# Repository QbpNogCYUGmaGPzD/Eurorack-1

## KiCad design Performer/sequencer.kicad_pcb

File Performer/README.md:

# Performer Eurorack Sequencer
Modified for PJ398/366 Jacks

[Revised BOM][BOM]. <- Please Read, important changes

[Orginal Hardware][westlicht]

This work is licensed under a [Creative Commons Attribution-NonCommercial-ShareAlike 4.0 International License][CCBYNCSA].

[westlicht]: https://github.com/westlicht/performer-hardware
[BOM]: https://docs.google.com/spreadsheets/d/1Ij7JMWFCJfHYTZfkfIStLHR7a7g3nUJE4kBo3WPE5Zw/edit?usp=sharing
[CCBYNCSA]: http://creativecommons.org/licenses/by-nc-sa/4.0/

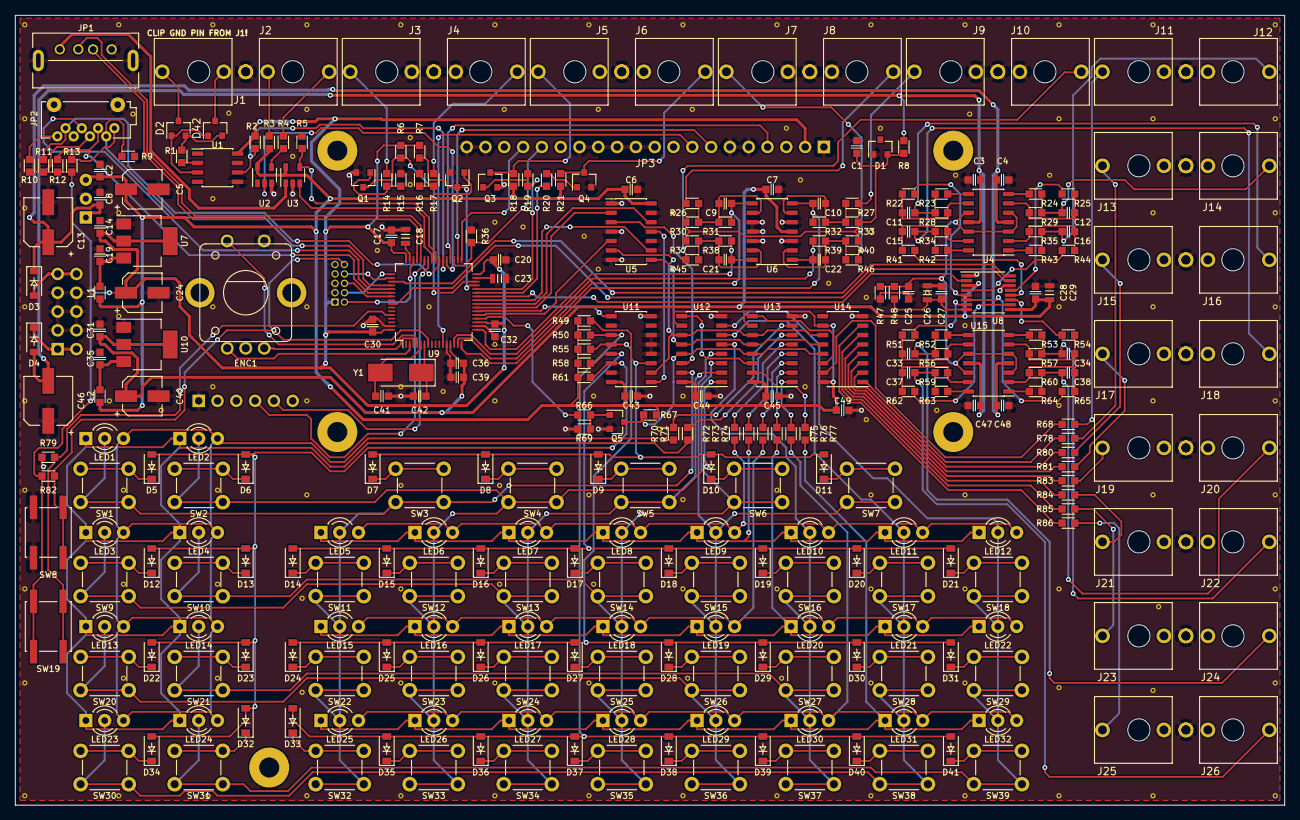
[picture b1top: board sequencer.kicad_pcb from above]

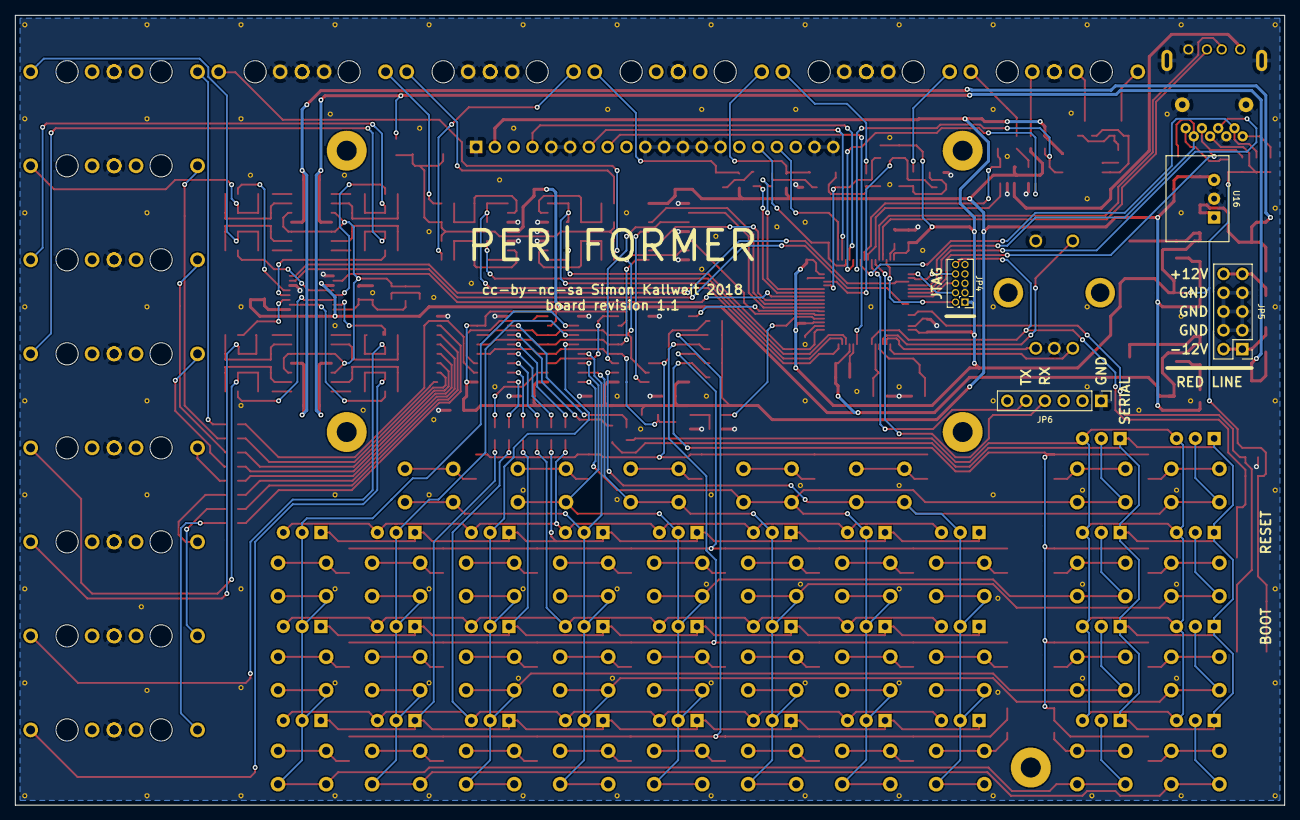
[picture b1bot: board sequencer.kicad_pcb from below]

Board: 2 copper layers, 171.4 x 106.7 mm, 305 parts (4 on the bottom side), 209 nets.

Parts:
C1, C2, C3, C4, C6, C7, C8, C14, C17, C19, C20, C25, C27, C28, C30, C31, C32, C35, C36, C43, C44, C45, C47, C48, C49: 100n; C_0603
C5, C24, C40: 22u; CP_Elec_5x5.8
C9, C10, C21, C22: 1n; C_0603
C11, C12, C15, C16, C33, C34, C37, C38, C41, C42: 18p; C_0603
C13, C46: 47u; CP_Elec_6.3x5.7
C18, C23, C26, C29: 2.2u; C_0805
C39: 1u; C_0603
D1: LM4040CIM3-10.0; SOT-23
D2, D42: BAT54S; SOT-23
D3, D4: 1N5819HW; D_SOD-123
D5, D6, D7, D8, D9, D10, D11, D12, D13, D14, D15, D16, D17, D18, D19, D20, D21, D22, D23, D24, D25, D26, D27, D28, D29, D30, D31, D32, D33, D34, D35, D36, D37, D38, D39, D40, D41: 1N4148; D_SOD-123
ENC1: PEC11R; ALPS_STEC12E08
J1, J2: PJ301CM; thonkiconn_tip3
J3, J4, J5, J6, J7, J8, J9, J10, J11, J12, J13, J14, J15, J16, J17, J18, J19, J20, J21, J22, J23, J24, J25, J26: PJ301BM; thonkiconn_tip3
JP1: USB_A; Kycon_USB_KUSBVLPX-AS1N
JP2: PJS008U-3000; PJS008U-3000-0
JP3: NHD-3.12-25664UC
JP4: JTAG; Pin_Header_Straight_2x05_Pitch1.27mm
JP5: POWER; Pin_Header_Straight_2x05_Pitch2.54mm
JP6: Serial / Bootloader; Pin_Header_Straight_1x06_Pitch2.54mm
L1, L2: Bead; R_0603
LED1, LED2, LED3, LED4, LED5, LED6, LED7, LED8, LED9, LED10, LED11, LED12, LED13, LED14, LED15, LED16, LED17, LED18, LED19, LED20, LED21, LED22, LED23, LED24, LED25, LED26, LED27, LED28, LED29, LED30, LED31, LED32: LTL1BEKVJNN
Q1, Q2, Q3, Q4, Q5: MMBT3904; SOT-23
R1, R3, R4, R23, R24, R42, R43, R52, R53, R63, R64: 220; R_0603
R2, R5, R6, R7, R19, R20, R36, R49, R50, R55, R58, R61, R66, R67, R79, R82: 10k; R_0603
R8, R18, R21, R68, R70, R71, R72, R73, R74, R75, R76, R77, R78, R80, R81, R83, R84, R85, R86: 1k; R_0603
R9, R15, R16: 1M; R_0603
R10, R11, R12, R13, R31, R32, R38, R39, R48: 33k; R_0603
R14, R17, R26, R27, R28, R29, R34, R35, R45, R46, R56, R57, R59, R60, R69: 100k; R_0603
R22, R25, R41, R44, R51, R54, R62, R65: 24k; R_0603
R30, R33, R37, R40: 200k; R_0603
R47: 22k; R_0603
SW1, SW2, SW3, SW4, SW5, SW6, SW7, SW9, SW10, SW11, SW12, SW13, SW14, SW15, SW16, SW17, SW18, SW20, SW21, SW22, SW23, SW24, SW25, SW26, SW27, SW28, SW29, SW30, SW31, SW32, SW33, SW34, SW35, SW36, SW37, SW38, SW39: TL1105; TL1105T
SW8, SW19: EVQQ2; SW_SPST_EVQQ2
U1: VO0600T; SOIC-8_3.9x4.9mm_Pitch1.27mm
U2: 74LV1T34; SOT-23-5
U3: STMPS2151; SOT-23-5
U4, U15: OPA4172; SOIC-14_3.9x8.7mm_Pitch1.27mm
U5: 74HCT125; SOIC-14_3.9x8.7mm_Pitch1.27mm
U6: MCP6004; SOIC-14_3.9x8.7mm_Pitch1.27mm
U7, U10: LM1117-3.3; SOT-223-3Lead_TabPin2
U8: DAC8568C; TSSOP-16_4.4x5mm_Pitch0.65mm
U9: STM32F405RGTx; LQFP-64_10x10mm_Pitch0.5mm
U11: 74HC165; SOIC-16_3.9x9.9mm_Pitch1.27mm
U12, U13, U14: 74HC595; SOIC-16_3.9x9.9mm_Pitch1.27mm
U16: R-78E5.0-1.0; R-78E-1.0
Y1: 8MHz; Crystal_SMD_Abracon_ABM3-2pin_5.0x3.2mm_HandSoldering

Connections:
+3.3VA: C7.1, C28.1, C29.1, C31.1, C36.1, C39.1, C40.1, U6.4, U8.3, U8.9, U9.13, U10.2
+3V3: C14.1, C17.1, C20.1, C24.1, C30.1, C32.1, JP2.4, JP3.2, JP4.1, R2.1, R6.1, R7.1, R10.2, R11.2, R12.2, R13.2, R82.1, SW19.2, U1.8, U7.2, U9.19, U9.32, U9.48, U9.64
+5V: C2.1, C5.1, C6.1, C43.1, C44.1, C45.1, C49.1, L1.2, L2.2, R3.1, R18.1, R21.1, R49.1, R50.1, R55.1, R58.1, R61.1, R67.1, U2.5, U3.5, U5.14, U11.16, U12.10, U12.16, U13.10, U13.16, U14.10, U14.16, U16.3
+12V: C4.1, C8.1, C13.1, C48.1, D3.1, U4.4, U15.4, U16.1
-12V: C3.2, C46.2, C47.2, D4.2, R8.1, U4.11, U15.11
/DAC/VBIAS: C25.1, R47.1, R48.2, U4.3, U4.5, U4.10, U4.12, U15.3, U15.5, U15.10, U15.12
AREF_-10V: C1.1, D1.2, R8.2, R30.2, R33.2, R37.2, R40.2
BOOT: R79.1, SW19.1, U9.60
CLK_IN: Q1.3, R6.2, U9.30
CLK_OUT: R19.2, U9.28
CV1: C16.1, J12.3, R35.1, R43.1
CV1_IN: C22.1, R39.1, U6.1, U9.14
CV2: C12.1, J14.3, R24.1, R29.1
CV2_IN: C9.1, R31.1, U6.8, U9.15
CV3: C11.1, J16.3, R23.1, R28.1
CV3_IN: C10.1, R32.1, U6.7, U9.16
CV4: C15.1, J18.3, R34.1, R42.1
CV4_IN: C21.1, R38.1, U6.14, U9.17
CV5: C38.1, J20.3, R60.1, R64.1
CV6: C34.1, J22.3, R53.1, R57.1
CV7: C33.1, J24.3, R52.1, R56.1
CV8: C37.1, J26.3, R59.1, R63.1
DAC1: R44.2, U8.4
DAC2: R25.2, U8.13
DAC3: R22.2, U8.5
DAC4: R41.2, U8.12
DAC5: R65.2, U8.6
DAC6: R54.2, U8.11
DAC7: R51.2, U8.7
DAC8: R62.2, U8.10
DAC_MOSI: U8.15, U9.57
DAC_SCK: U8.16, U9.51
DAC_SYNC: U8.2, U9.26
ENC_A: ENC1.A, U9.2
ENC_B: ENC1.B, U9.3
ENC_SW: ENC1.SW1, U9.4
GATE1: R68.2, U14.15
GATE2: R78.2, U14.1
GATE3: R80.2, U14.2
GATE4: R81.2, U14.3
GATE5: R83.2, U14.4
GATE6: R84.2, U14.5
GATE7: R85.2, U14.6
GATE8: R86.2, U14.7
GCOL0: LED25.3, LED26.3, LED27.3, LED28.3, LED29.3, LED30.3, LED31.3, LED32.3, R76.1
GCOL1: LED15.3, LED16.3, LED17.3, LED18.3, LED19.3, LED20.3, LED21.3, LED22.3, R74.1
GCOL2: LED5.3, LED6.3, LED7.3, LED8.3, LED9.3, LED10.3, LED11.3, LED12.3, R72.1
GCOL3: LED1.3, LED2.3, LED3.3, LED4.3, LED13.3, LED14.3, LED23.3, LED24.3, R70.1
GND: C1.2, C2.2, C3.1, C4.2, C5.2, C6.2, C7.2, C8.2, C13.2, C14.2, C17.2, C18.1, C19.2, C20.2, C23.1, C24.2, C25.2, C26.2, C27.2, C28.2, C29.2, C30.2, C31.2, C32.2, C35.2, C36.2, C39.2, C40.2, C41.1, C42.1, C43.2, C44.2, C45.2, C46.1, C47.1, C48.2, C49.2, D1.1, ENC1.C, ENC1.SW2, J1.1, J2.1, J3.1, J3.2, J4.1, J4.2, J5.1, J6.1, J7.1, J7.2, J8.1, J8.2, J9.1, J9.2, J10.1, J10.2, J11.1, J12.1, J13.1, J14.1, J15.1, J16.1, J17.1, J18.1, J19.1, J20.1, J21.1, J22.1, J23.1, J24.1, J25.1, J26.1, JP1.4, JP1.5, JP2.6, JP2.9, JP3.1, JP3.5, JP3.6, JP3.10, JP3.11, JP3.12, JP3.13, JP3.14, JP3.19, JP3.20, JP4.3, JP4.5, JP4.9, JP5.3, JP5.4, JP5.5, JP5.6, JP5.7, JP5.8, JP6.1, Q1.2, Q2.2, Q3.2, Q4.2, Q5.2, R5.2, R9.1, R15.2, R16.2, R36.2, R47.2, R69.2, R79.2, SW8.1, U1.5, U2.3, U3.2, U5.1, U5.4, U5.7, U5.10, U5.13, U6.3, U6.5, U6.10, U6.11, U6.12, U7.1, U8.1, U8.14, U9.12, U9.18, U9.63, U10.1, U11.4, U11.5, U11.6, U11.8, U11.10, U11.15, U12.8, U13.8, U14.8, U16.2
LCD_CS: JP3.17, U9.33
LCD_DC: JP3.4, U9.36
LCD_MOSI: JP3.8, U9.11
LCD_RES: JP3.16, R36.1, U9.35
LCD_SCK: JP3.7, U9.34
MIDI_RX: R2.2, U1.6, U9.38
MIDI_TX: U2.2, U9.37
unnamed: C9.2, R26.1, R30.1, R31.2, U6.9
unnamed: C10.2, R27.1, R32.2, R33.1, U6.6
unnamed: C11.2, R22.1, R28.2, U4.9
unnamed: C12.2, R25.1, R29.2, U4.6
unnamed: C15.2, R34.2, R41.1, U4.13
unnamed: C16.2, R35.2, R44.1, U4.2
unnamed: C18.2, U9.47
unnamed: C19.1, L1.1, U7.3
unnamed: C21.2, R37.1, R38.2, R45.1, U6.13
unnamed: C22.2, R39.2, R40.1, R46.1, U6.2
unnamed: C23.2, U9.31
unnamed: C26.1, C27.1, R48.1, U8.8
unnamed: C33.2, R51.1, R56.2, U15.9
unnamed: C34.2, R54.1, R57.2, U15.6
unnamed: C35.1, L2.1, U10.3
unnamed: C37.2, R59.2, R62.1, U15.13
unnamed: C38.2, R60.2, R65.1, U15.2
unnamed: D2.1, D42.1, U1.3
unnamed: D2.2, D42.2, R1.2
unnamed: D2.3, J1.3
unnamed: D3.2, JP5.9, JP5.10
unnamed: D4.1, JP5.1, JP5.2
unnamed: D5.1, SW1.3, SW1.4
unnamed: D6.1, SW2.3, SW2.4
unnamed: D7.1, SW3.3, SW3.4
unnamed: D8.1, SW4.3, SW4.4
unnamed: D9.1, SW5.3, SW5.4
unnamed: D10.1, SW6.3, SW6.4
unnamed: D11.1, SW7.3, SW7.4
unnamed: D12.1, SW9.3, SW9.4
unnamed: D13.1, SW10.3, SW10.4
unnamed: D14.1, SW11.3, SW11.4
unnamed: D15.1, SW12.3, SW12.4
unnamed: D16.1, SW13.3, SW13.4
unnamed: D17.1, SW14.3, SW14.4
unnamed: D18.1, SW15.3, SW15.4
unnamed: D19.1, SW16.3, SW16.4
unnamed: D20.1, SW17.3, SW17.4
unnamed: D21.1, SW18.3, SW18.4
unnamed: D22.1, SW20.3, SW20.4
unnamed: D23.1, SW21.3, SW21.4
unnamed: D24.1, SW22.3, SW22.4
unnamed: D25.1, SW23.3, SW23.4
unnamed: D26.1, SW24.3, SW24.4
unnamed: D27.1, SW25.3, SW25.4
unnamed: D28.1, SW26.3, SW26.4
unnamed: D29.1, SW27.3, SW27.4
unnamed: D30.1, SW28.3, SW28.4
unnamed: D31.1, SW29.3, SW29.4
unnamed: D32.1, SW31.3, SW31.4
unnamed: D33.1, SW32.3, SW32.4
unnamed: D34.1, SW30.3, SW30.4
unnamed: D35.1, SW33.3, SW33.4
unnamed: D36.1, SW34.3, SW34.4
unnamed: D37.1, SW35.3, SW35.4
unnamed: D38.1, SW36.3, SW36.4
unnamed: D39.1, SW37.3, SW37.4
unnamed: D40.1, SW38.3, SW38.4
unnamed: D41.1, SW39.3, SW39.4
unnamed: D42.3, J1.2
unnamed: J2.2, R3.2
unnamed: J2.3, R4.2
unnamed: J3.3, R14.2
unnamed: J4.3, R17.2
unnamed: J5.3, Q3.3, R18.2
unnamed: J6.3, Q4.3, R21.2
unnamed: J7.3, R46.2
unnamed: J8.3, R26.2
unnamed: J9.3, R27.2
unnamed: J10.3, R45.2
unnamed: J11.3, R68.1
unnamed: J13.3, R78.1
unnamed: J15.3, R80.1
unnamed: J17.3, R81.1
unnamed: J19.3, R83.1
unnamed: J21.3, R84.1
unnamed: J23.3, R85.1
unnamed: J25.3, R86.1
unnamed: JP2.1, R13.1
unnamed: JP2.8, R10.1
unnamed: Q1.1, R14.1, R15.1
unnamed: Q2.1, R16.1, R17.1
unnamed: Q3.1, R19.1
unnamed: Q4.1, R20.1
unnamed: Q5.1, R66.1, R69.1
unnamed: Q5.3, R67.2, U12.13, U13.13, U14.13
unnamed: R1.1, U1.2
unnamed: R4.1, U2.4
unnamed: R23.2, U4.8
unnamed: R24.2, U4.7
unnamed: R42.2, U4.14
unnamed: R43.2, U4.1
unnamed: R52.2, U15.8
unnamed: R53.2, U15.7
unnamed: R63.2, U15.14
unnamed: R64.2, U15.1
unnamed: R70.2, U13.7
unnamed: R71.2, U13.6
unnamed: R72.2, U13.5
unnamed: R73.2, U13.4
unnamed: R74.2, U13.3
unnamed: R75.2, U13.2
unnamed: R76.2, U13.1
unnamed: R77.2, U13.15
unnamed: U5.11, U11.1
unnamed: U5.6, U11.2, U12.11, U13.11, U14.11
unnamed: U12.9, U13.14
unnamed: U5.8, U12.12, U13.12, U14.12
unnamed: U5.3, U12.14
unnamed: U13.9, U14.14
OSC_IN: C41.2, U9.5, Y1.2
OSC_OUT: C42.2, U9.6, Y1.1
RCOL0: LED25.1, LED26.1, LED27.1, LED28.1, LED29.1, LED30.1, LED31.1, LED32.1, R77.1
RCOL1: LED15.1, LED16.1, LED17.1, LED18.1, LED19.1, LED20.1, LED21.1, LED22.1, R75.1
RCOL2: LED5.1, LED6.1, LED7.1, LED8.1, LED9.1, LED10.1, LED11.1, LED12.1, R73.1
RCOL3: LED1.1, LED2.1, LED3.1, LED4.1, LED13.1, LED14.1, LED23.1, LED24.1, R71.1
RESET: JP4.10, R82.2, SW8.2, U9.7
RES_IN: Q2.3, R7.2, U9.29
RES_OUT: R20.2, U9.27
ROW0: LED1.2, LED5.2, LED15.2, LED25.2, SW1.1, SW1.2, SW3.1, SW3.2, SW11.1, SW11.2, SW22.1, SW22.2, SW32.1, SW32.2, U12.15
ROW1: LED2.2, LED6.2, LED16.2, LED26.2, SW2.1, SW2.2, SW4.1, SW4.2, SW12.1, SW12.2, SW23.1, SW23.2, SW33.1, SW33.2, U12.1
ROW2: LED3.2, LED7.2, LED17.2, LED27.2, SW5.1, SW5.2, SW9.1, SW9.2, SW13.1, SW13.2, SW24.1, SW24.2, SW34.1, SW34.2, U12.2
ROW3: LED4.2, LED8.2, LED18.2, LED28.2, SW6.1, SW6.2, SW10.1, SW10.2, SW14.1, SW14.2, SW25.1, SW25.2, SW35.1, SW35.2, U12.3
ROW4: LED9.2, LED13.2, LED19.2, LED29.2, SW7.1, SW7.2, SW15.1, SW15.2, SW20.1, SW20.2, SW26.1, SW26.2, SW36.1, SW36.2, U12.4
ROW5: LED10.2, LED14.2, LED20.2, LED30.2, SW16.1, SW16.2, SW21.1, SW21.2, SW27.1, SW27.2, SW37.1, SW37.2, U12.5
ROW6: LED11.2, LED21.2, LED23.2, LED31.2, SW17.1, SW17.2, SW28.1, SW28.2, SW30.1, SW30.2, SW38.1, SW38.2, U12.6
ROW7: LED12.2, LED22.2, LED24.2, LED32.2, SW18.1, SW18.2, SW29.1, SW29.2, SW31.1, SW31.2, SW39.1, SW39.2, U12.7
SCOL0: D33.2, D35.2, D36.2, D37.2, D38.2, D39.2, D40.2, D41.2, R50.2, U11.11
SCOL1: D24.2, D25.2, D26.2, D27.2, D28.2, D29.2, D30.2, D31.2, R55.2, U11.12
SCOL2: D14.2, D15.2, D16.2, D17.2, D18.2, D19.2, D20.2, D21.2, R58.2, U11.13
SCOL3: D5.2, D6.2, D12.2, D13.2, D22.2, D23.2, D32.2, D34.2, R61.2, U11.14
SCOL4: D7.2, D8.2, D9.2, D10.2, D11.2, R49.2, U11.3
SDIO_CD: JP2.2, R9.2, U9.52
SDIO_CLK: JP2.5, U9.53
SDIO_CMD: JP2.3, R12.1, U9.54
SDIO_D0: JP2.7, R11.1, U9.39
SR_LATCH: U5.9, U9.25
SR_LOAD: U5.12, U9.24
SR_MISO: U9.22, U11.9
SR_MOSI: U5.2, U9.23
SR_OE: R66.2, U9.20
SR_SCK: U5.5, U9.21
SYS_JTCK: JP4.4, U9.49
SYS_JTDI: JP4.8, U9.50
SYS_JTDO: JP4.6, U9.55
SYS_JTMS: JP4.2, U9.46
SYS_RX: JP6.4, U9.43
SYS_TX: JP6.5, U9.42
USB_5V: JP1.1, U3.1
USB_D+: JP1.3, U9.45
USB_D-: JP1.2, U9.44
USB_PWR_EN: R5.1, U3.4, U9.40
USB_PWR_FAULT: U3.3, U9.41

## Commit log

2018-02-24 GridEX
2018-03-08 Added BOM
2018-03-08 typos
2018-03-08 more typos
2018-03-08 organize
2018-04-10 fixed
2019-04-06 liscense stuff
2019-04-06 More License stuff
2019-04-06 KiCad files
2019-04-08 CleanUp
2019-04-08 Personalize

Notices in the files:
Performer/sequencer.kicad_pcb:
cc-by-nc-sa Simon Kallweit 2018
